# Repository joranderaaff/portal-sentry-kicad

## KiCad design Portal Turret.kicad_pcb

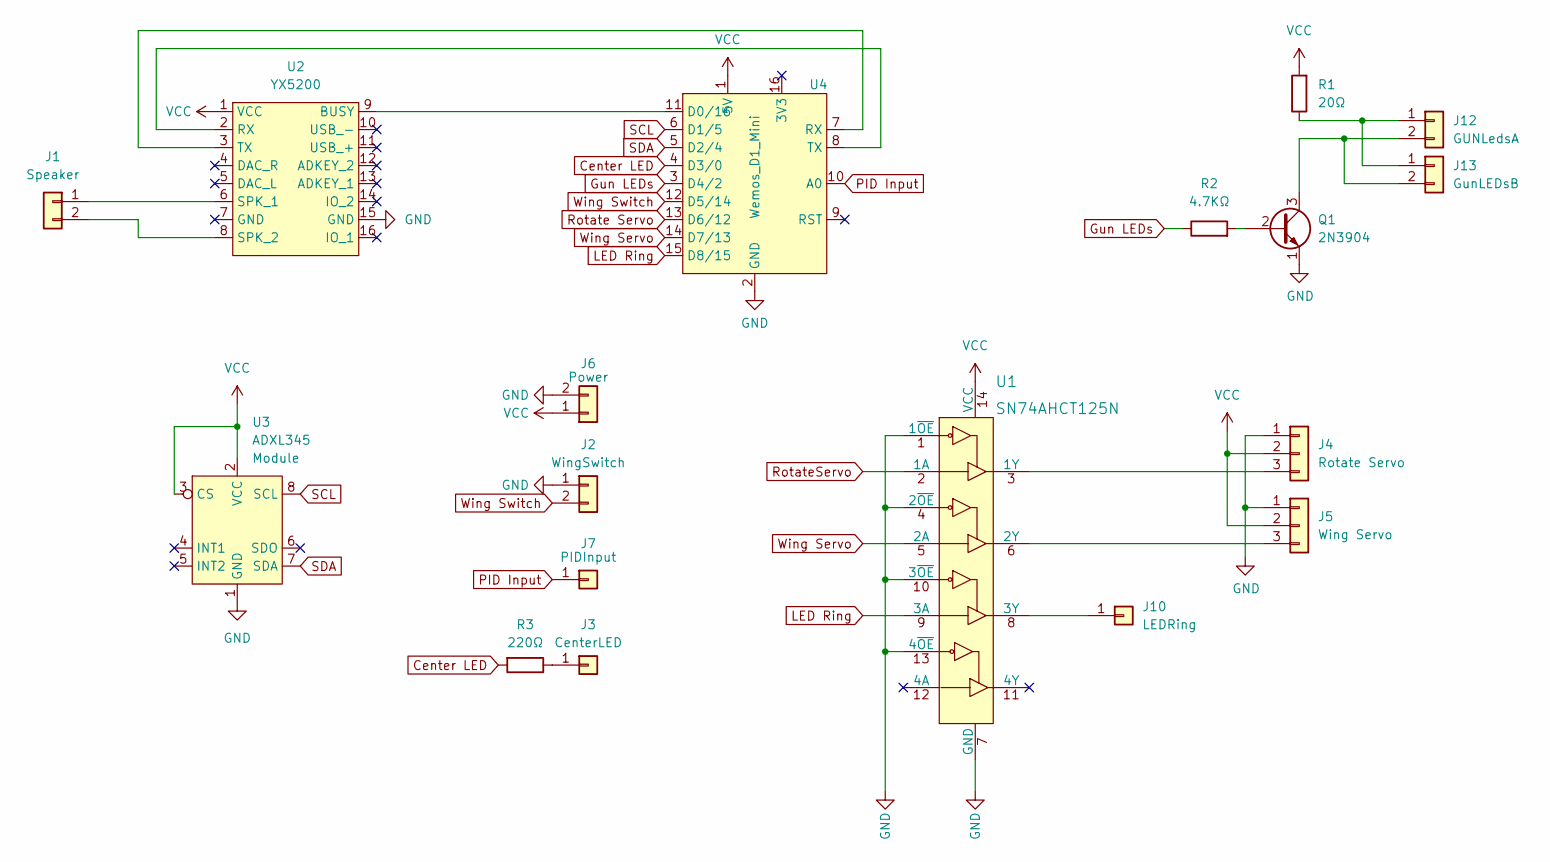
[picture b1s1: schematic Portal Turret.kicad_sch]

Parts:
J1: Speaker; PinHeader_1x02_P2.54mm_Vertical
J2: WingSwitch; PinHeader_1x02_P2.54mm_Vertical
J3: CenterLED; PinHeader_1x01_P2.54mm_Vertical
J4: Rotate Servo; PinHeader_1x03_P2.54mm_Vertical
J5: Wing Servo; PinHeader_1x03_P2.54mm_Vertical
J6: Power; PinHeader_1x02_P2.54mm_Vertical
J7: PIDInput; PinHeader_1x01_P2.54mm_Vertical
J10: LEDRing; PinHeader_1x01_P2.54mm_Vertical
J12: GUNLedsA; PinHeader_1x02_P2.54mm_Vertical
J13: GunLEDsB; PinHeader_1x02_P2.54mm_Vertical
Q1: 2N3904; TO-92_Inline
R1: 20Ω; R_Axial_DIN0207_L6.3mm_D2.5mm_P7.62mm_Horizontal
R2: 4.7KΩ; R_Axial_DIN0207_L6.3mm_D2.5mm_P7.62mm_Horizontal
R3: 220Ω; R_Axial_DIN0207_L6.3mm_D2.5mm_P7.62mm_Horizontal
U1: SN74AHCT125N; DIP-14_W7.62mm; MPN SN74AHCT125N; Digi-Key_PN 296-4655-5-ND
U2: YX5200
U3: ADXL345
U4: Wemos_D1_Mini; WemosD1MiniV3

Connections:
Center LED: R3.2, U4.4 (D3/0)
GND: J2.1, J4.1, J5.1, J6.2, Q1.1 (E), U1.1 (1~OE), U1.4 (2~OE), U1.7 (GND), U1.10 (3~OE), U1.13 (4~OE), U2.15 (GND), U3.1 (GND), U4.2 (GND)
Gun LEDs: R2.1, U4.3 (D4/2)
LED Ring: U1.9 (3A), U4.15 (D8/15)
unnamed: J1.1, U2.6 (SPK_1)
unnamed: J1.2, U2.8 (SPK_2)
unnamed: J3.1, R3.1
unnamed: J4.3, U1.3 (1Y)
unnamed: J5.3, U1.6 (2Y)
unnamed: J10.1, U1.8 (3Y)
unnamed: J12.1, J13.1, R1.1
unnamed: J12.2, J13.2, Q1.3 (C)
unnamed: Q1.2 (B), R2.2
unnamed: U2.2 (RX), U4.8 (TX)
unnamed: U2.3 (TX), U4.7 (RX)
unnamed: U2.9 (BUSY), U4.11 (D0/16)
PID Input: J7.1, U4.10 (A0)
Rotate Servo: U4.13 (D6/12)
RotateServo: U1.2 (1A)
SCL: U3.8 (SCL), U4.6 (D1/5)
SDA: U3.7 (SDA), U4.5 (D2/4)
VCC: J4.2, J5.2, J6.1, R1.2, U1.14 (VCC), U2.1 (VCC), U3.2 (VCC), U3.3 (CS), U4.1 (5V)
Wing Servo: U1.5 (2A), U4.14 (D7/13)
Wing Switch: J2.2, U4.12 (D5/14)

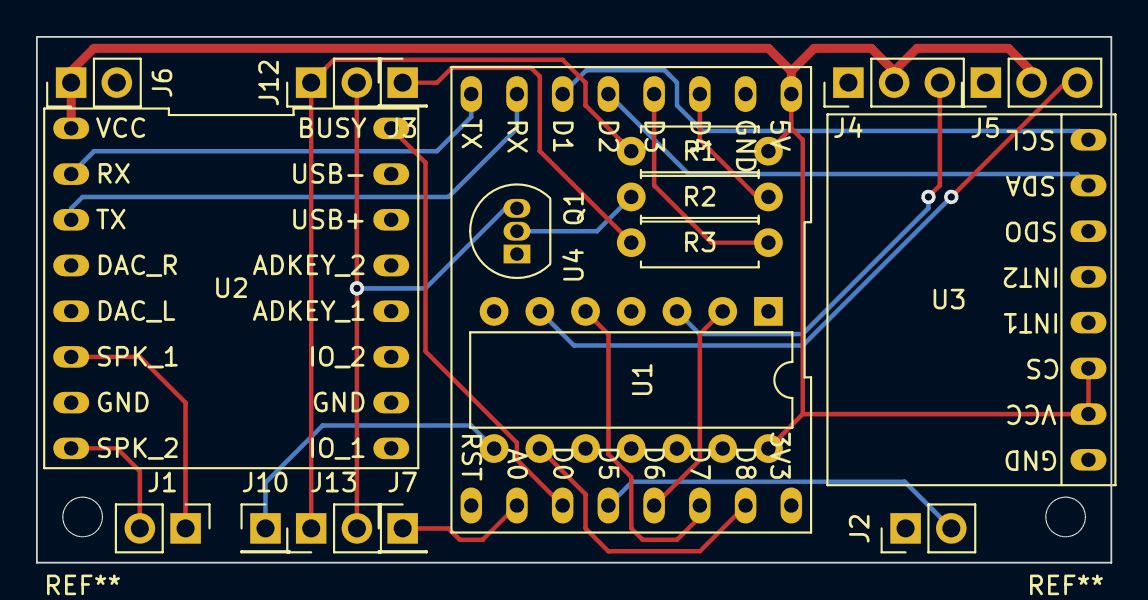
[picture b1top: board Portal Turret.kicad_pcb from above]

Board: 2 copper layers, 59.7 x 29.2 mm, 18 parts (0 on the bottom side), 22 nets.
